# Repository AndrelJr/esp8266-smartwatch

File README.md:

# ESP8266 Smartwatch
## Pictures / Videos

#### YouTube Videos
* [Building the watch](https://www.youtube.com/watch?v=ve8lzYSVnGo)
* [Minetest controller](https://www.youtube.com/watch?v=W3ALEUs_7kA)
* [Compass test](https://www.youtube.com/watch?v=Mj3a6peVI30)

# Hardware
## Specifications
* ESP8266 with 32Mbit of flash memory
* MPU-9250 gyroscope, accelerometer with integrated AK8963 magnetometer
* RV-3029-C2 Real Time Clock
* FT232RQ for USB communication
* SSD1306 OLED Display, 128x64
* 3 Hardware Buttons
* MCP73831 LiPo charger
* 250mAh LiPo battery
* Dimensions: 35 * 39 * 11mm
* WiFi with chip antenna
* Vibration Motor

See `board/v1/README.md` for a detailed parts list.

# Software
The firmwares in `firmwares` use the [esp-open-sdk](https://github.com/pfalcon/esp-open-sdk). You may need to customize the `main.c` files to reflect your WiFi configuration. This is mainly a hardware project and not a software project, so the firmwares are primarily meant to be demos for the hardware features of the watch. Firmwares can be uploaded using [esptool](https://github.com/themadinventor/esptool) and debugging is possible with a serial port terminal like [espterm](https://github.com/Jeija/espterm).

# Attribution
* `libesphttpd` (used in the minetest firmware) was [written by Spritetm](https://github.com/Spritetm/libesphttpd) and contributors and is licensed under "THE BEER-WARE LICENSE".
* `httpclient.c` / `httpclient.h` (included in all firmwares) was [written by Caerbannog](https://github.com/Caerbannog/esphttpclient) and contributors and is licensed under "THE BEER-WARE LICENSE".
* `i2c_master.h` / `i2c_master.c` was written by Espressif Systems

# License
The hardware design (schematic, PCB design, footprints, ...) is licensed under a [Creative Commons Attribution-NonCommercial-ShareAlike 4.0 International License](http://creativecommons.org/licenses/by-nc-sa/4.0/) (CC-BY-NC-SA).

The firmware source code is licensed under the [MIT License](https://opensource.org/licenses/MIT).

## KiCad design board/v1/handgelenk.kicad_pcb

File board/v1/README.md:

# ESP8266 Smartwatch Hardware V1
## Parts list
* 1x PCB
* 1x ESP8266EX WiFi SoC
* 1x FT232RQ USB to UART
* 1x MCP73831 LiPo charger
* 1x TLV70233 SOT-23 LDO (or compatible)
* 1x W25Q32BV 32Mbit flash
* 1x InvenSense MPU-9250 9-axis sensor
* 1x RV-3029-C2 RTC
* 1x 26MHz crystal 2.5x2mm
* 1x Rainsun AN9520 Chip Antenna
* 3x TS-015A / WS-TUS 434331045822 Buttons
* 1x muRata BLM21PG 600 EMI Suppression Filter
* 1x USB Micro B connector, SMD
* 1x EastRising SSD1306 OLED
* 1x 250mAh LiPo
* 1x Low power vibration motor
* 1x BC849 SOT-23 NPN transistor
* 6x 100nF 0603 Capacitor
* 3x 10nF 0603 Capacitor
* 2x 4.7µF 0603 Capacitor
* 1x 100µF 1206 Capacitor
* 1x 10µF 1206 Capacitor
* 1x 5.6pF 0402 Capacitor
* 2x 10pF 0402 Capacitor
* 5x 1µF 0603 Capacitor
* 1x 2.2µF 0603 Capacitor
* 3x 1N4148 SOD-323 Diode
* 2x 1K 0603 Resistor
* 1x 12K 0603 Resistor
* 1x 3.3K 0603 Resistor
* 1x 300 0603 Resistor
* 1x 200 0603 Resistor
* 1x 330K 0603 Resistor
* 1x 100K 0603 Resistor
* 4x 10K 0603 Resistor
* 1x 50 0603 Resistor
* 1x 390K 0603 Resistor

## Production files
See the `gerber` directory for original PCB production files. My PCBs were manufactured by Seeedstudio's PCB service.

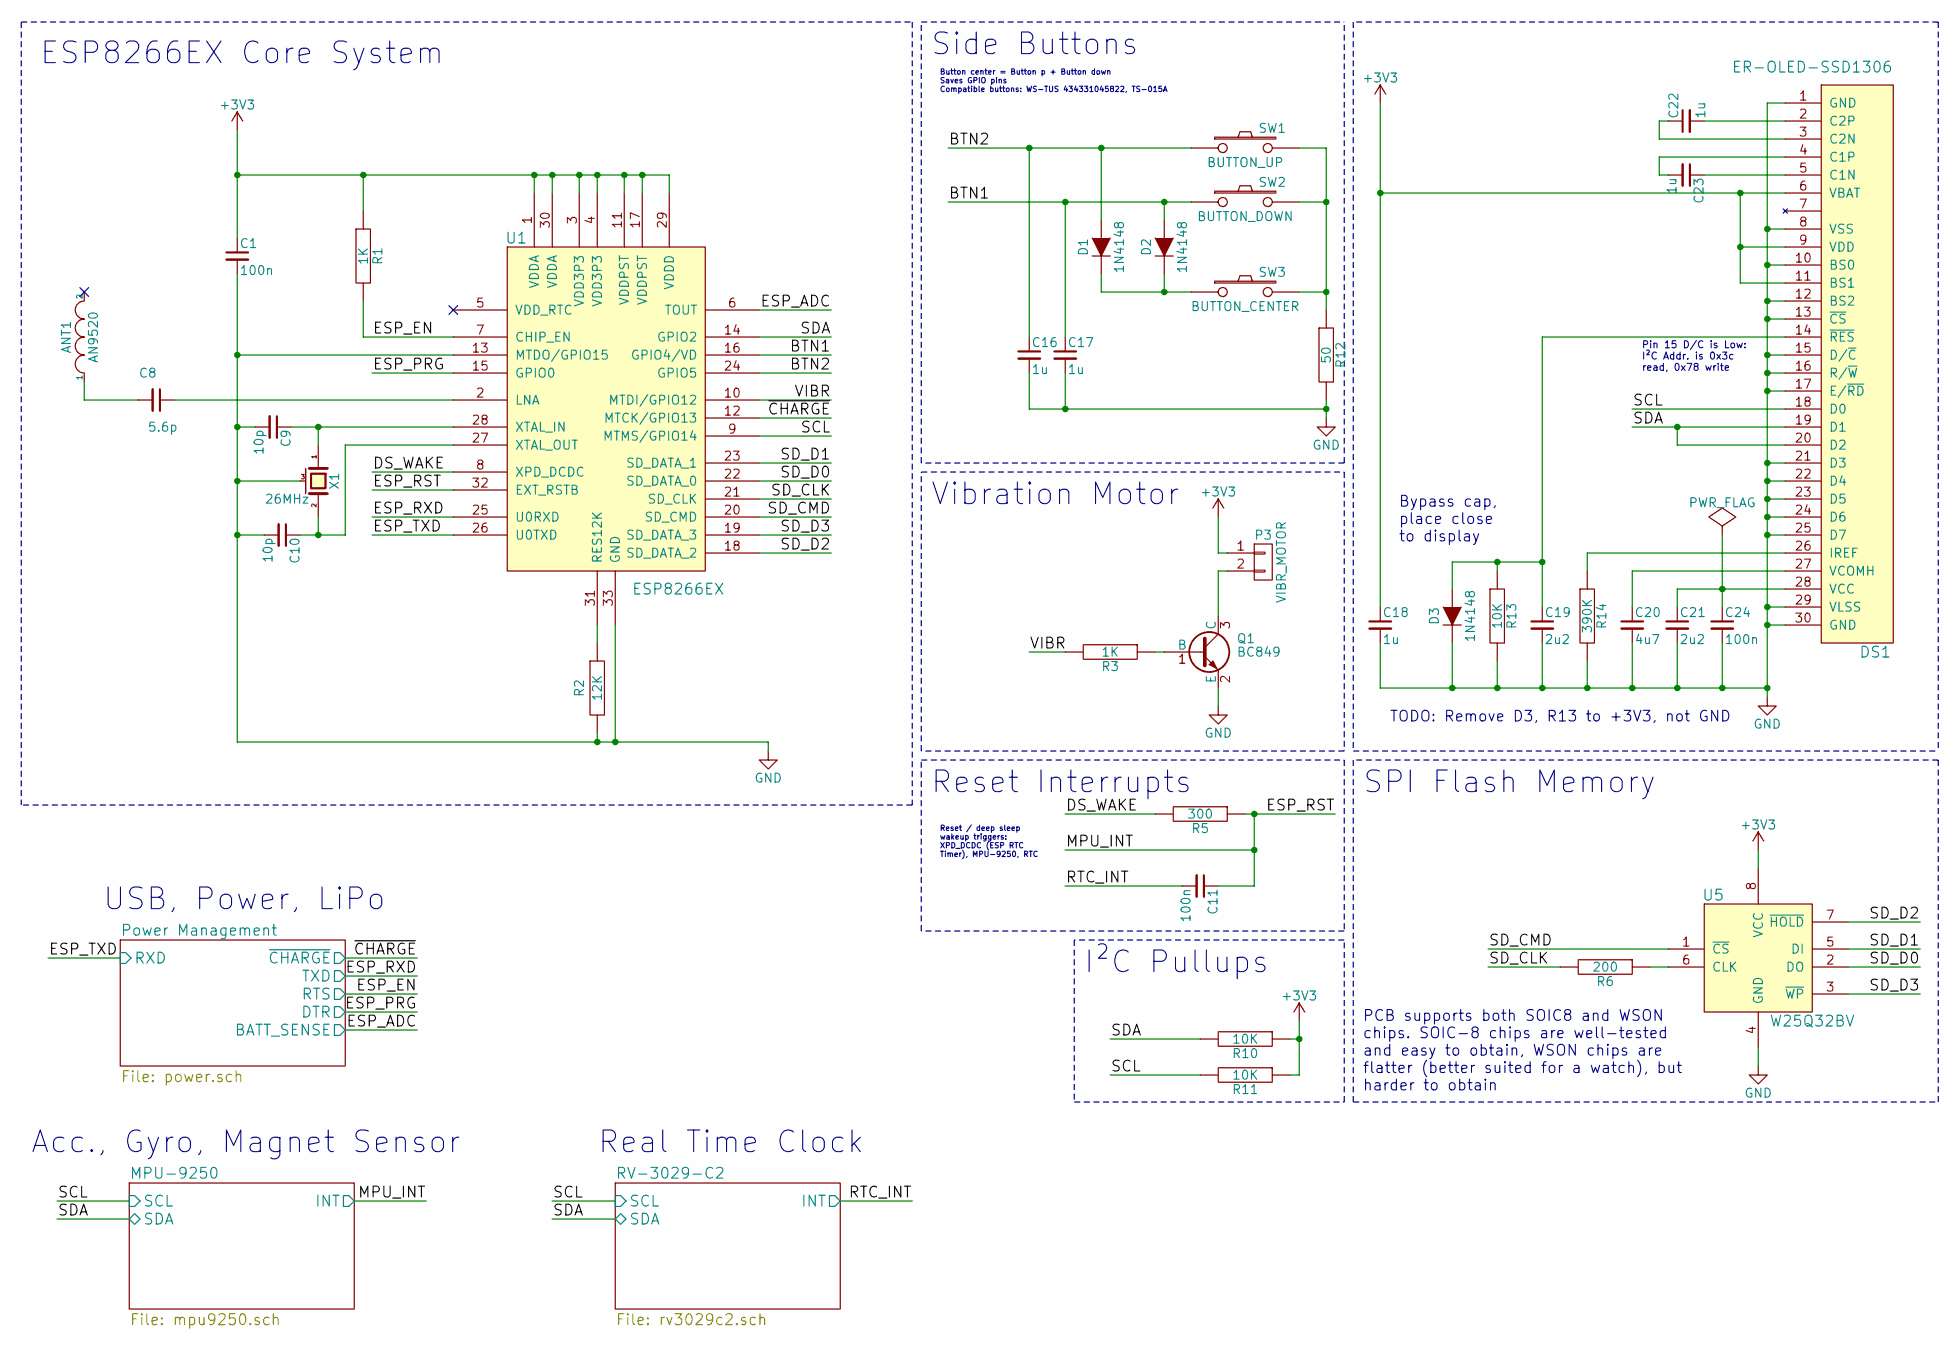
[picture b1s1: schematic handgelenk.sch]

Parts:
ANT1: AN9520; an9520
C1, C11, C24: 100n; C_0603
C8: 5.6p; C_0402
C9, C10: 10p; C_0402
C16, C17, C18, C22, C23: 1u; C_0603
C19, C21: 2u2; C_0603
C20: 4u7; C_0603
D1, D2, D3: 1N4148; SOD-323
DS1: ER-OLED-SSD1306; er-oled-ssd1306
P3: VIBR_MOTOR; Pin_Header_Straight_1x02
Q1: BC849; SOT-23
R1, R3: 1K; R_0603
R2: 12K; R_0603
R5: 300; R_0603
R6: 200; R_0603
R10, R11, R13: 10K; R_0603
R12: 50; R_0603
R14: 390K; R_0603
SW1: BUTTON_UP; ts015a
SW2: BUTTON_DOWN; ts015a
SW3: BUTTON_CENTER; ts015a
U1: ESP8266EX; QFN-32-1EP_5x5mm_Pitch0.5mm
U5: W25Q32BV; wson8_5x6
X1: 26MHz; crystal_2.5x2

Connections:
+3V3: C1.1, C18.1, DS1.6 (VBAT), DS1.9 (VDD), DS1.11 (BS1), P3.1, R1.1, R10.1, R11.1, U1.1 (VDDA), U1.3 (VDD3P3), U1.4 (VDD3P3), U1.11 (VDDPST), U1.17 (VDDPST), U1.29 (VDDD), U1.30 (VDDA), U5.8 (VCC); also elsewhere on the board
/BTN1: C17.1, D2.2 (A), SW2.1, U1.16 (GPIO4/VD)
/BTN2: C16.1, D1.2 (A), SW1.1, U1.24 (GPIO5)
/DS_WAKE: R5.2, U1.8 (XPD_DCDC)
/MPU-9250/INT: C11.1, R5.1, U1.32 (EXT_RSTB); also elsewhere on the board
/MPU-9250/SCL: DS1.18 (D0), R11.2, U1.9 (MTMS/GPIO14); also elsewhere on the board
/MPU-9250/SDA: DS1.19 (D1), DS1.20 (D2), R10.2, U1.14 (GPIO2); also elsewhere on the board
/Power Management/BATT_SENSE: U1.6 (TOUT); also elsewhere on the board
/Power Management/DTR: U1.15 (GPIO0); also elsewhere on the board
/Power Management/RTS: R1.2, U1.7 (CHIP_EN); also elsewhere on the board
/Power Management/RXD: U1.26 (U0TXD); also elsewhere on the board
/Power Management/TXD: U1.25 (U0RXD); also elsewhere on the board
/Power Management/~CHARGE: U1.12 (MTCK/GPIO13); also elsewhere on the board
/RV-3029-C2/INT: C11.2; also elsewhere on the board
/SD_CLK: R6.2, U1.21 (SD_CLK)
/SD_CMD: U1.20 (SD_CMD), U5.1 (~CS)
/SD_D0: U1.22 (SD_DATA_0), U5.2 (DO)
/SD_D1: U1.23 (SD_DATA_1), U5.5 (DI)
/SD_D2: U1.18 (SD_DATA_2), U5.7 (~HOLD)
/SD_D3: U1.19 (SD_DATA_3), U5.3 (~WP)
/VIBR: R3.2, U1.10 (MTDI/GPIO12)
GND: C1.2, C9.2, C10.2, C16.2, C17.2, C18.2, C19.2, C20.2, C21.2, C24.2, D3.1 (K), DS1.1 (GND), DS1.8 (VSS), DS1.10 (BS0), DS1.12 (BS2), DS1.13 (~CS), DS1.15 (D/~C), DS1.16 (R/~W), DS1.17 (E/~RD), DS1.21 (D3), DS1.22 (D4), DS1.23 (D5), DS1.24 (D6), DS1.25 (D7), DS1.29 (VLSS), DS1.30 (GND), Q1.2 (E), R2.2, R12.2, R13.2, R14.2, U1.13 (MTDO/GPIO15), U1.33 (GND), U5.4 (GND), X1.3 (case); also elsewhere on the board
unnamed: ANT1.1, C8.2
unnamed: C8.1, U1.2 (LNA)
unnamed: C9.1, U1.28 (XTAL_IN), X1.1
unnamed: C10.1, U1.27 (XTAL_OUT), X1.2
unnamed: C19.1, D3.2 (A), DS1.14 (~RES), R13.1
unnamed: C20.1, DS1.27 (VCOMH)
unnamed: C21.1, C24.1, DS1.28 (VCC)
unnamed: C22.1, DS1.3 (C2N)
unnamed: C22.2, DS1.2 (C2P)
unnamed: C23.1, DS1.5 (C1N)
unnamed: C23.2, DS1.4 (C1P)
unnamed: D1.1 (K), D2.1 (K), SW3.1
unnamed: DS1.26 (IREF), R14.1
unnamed: P3.2, Q1.3 (C)
unnamed: Q1.1 (B), R3.1
unnamed: R2.1, U1.31 (RES12K)
unnamed: R6.1, U5.6 (CLK)
unnamed: R12.1, SW1.2, SW2.2, SW3.2

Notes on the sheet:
Reset / deep sleep wakeup triggers: XPD_DCDC (ESP RTC Timer), MPU-9250, RTC
PCB supports both SOIC8 and WSON chips. SOIC-8 chips are well-tested and easy to obtain, WSON chips are flatter (better suited for a watch), but harder to obtain
SPI Flash Memory
Pin 15 D/C is Low: I²C Addr. is 0x3c read, 0x78 write
Bypass cap, place close to display
Button center = Button p + Button down Saves GPIO pins Compatible buttons: WS-TUS 434331045822, TS-015A
Side Buttons
Vibration Motor
ESP8266EX Core System
I²C Pullups
Reset Interrupts
Acc., Gyro, Magnet Sensor
Real Time Clock
USB, Power, LiPo
TODO: Remove D3, R13 to +3V3, not GND

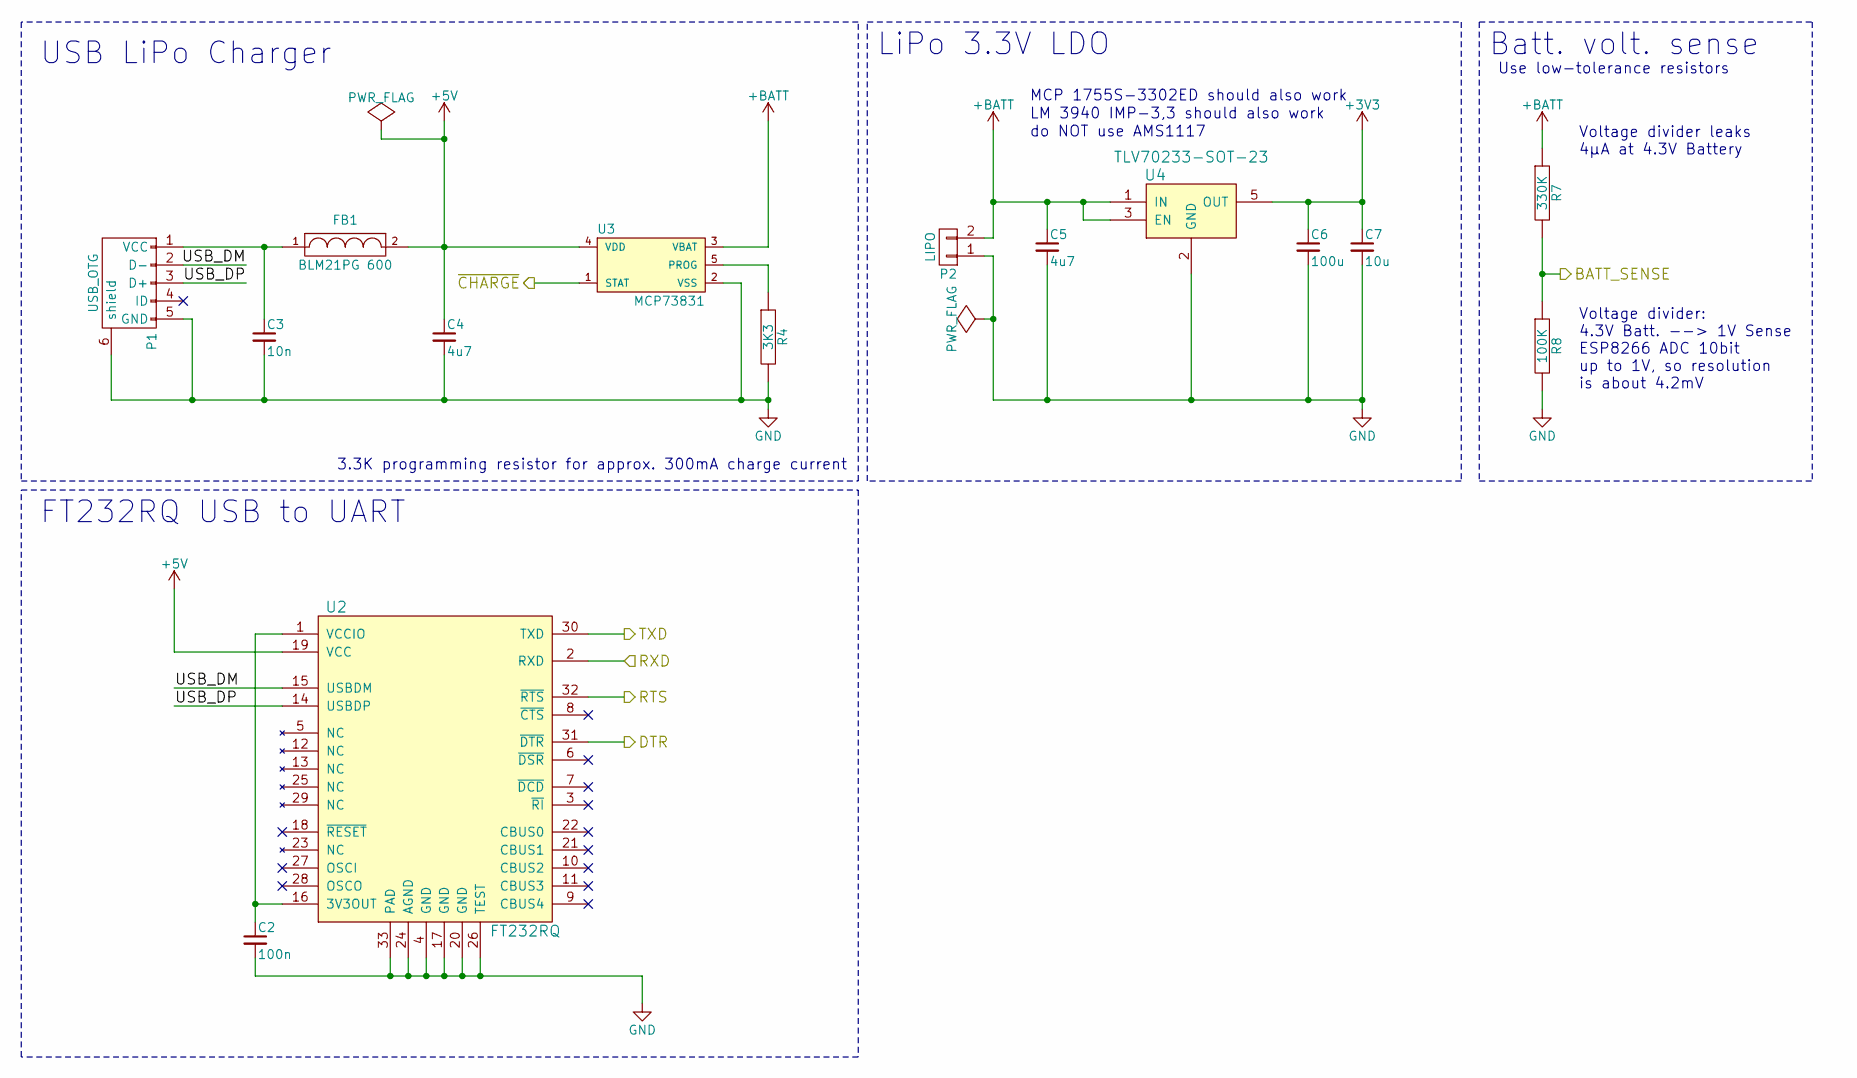
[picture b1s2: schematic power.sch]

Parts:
C2: 100n; C_0603
C3: 10n; C_0603
C4, C5: 4u7; C_0603
C6: 100u; C_1206
C7: 10u; C_0603
FB1: BLM21PG 600; C_0805
P1: USB_OTG; USB_Micro-B
P2: LIPO; Pin_Header_Straight_1x02
R4: 3K3; R_0603
R7: 330K; R_0603
R8: 100K; R_0603
U2: FT232RQ; QFN-32-1EP_5x5mm_Pitch0.5mm
U3: MCP73831; SOT-23-5
U4: TLV70233-SOT-23; SOT-23-5

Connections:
+3V3: C6.1, C7.1, U4.5 (OUT); also elsewhere on the board
+5V: C4.1, FB1.2, U2.19 (VCC), U3.4 (VDD)
+BATT: C5.1, P2.2, R7.1, U3.3 (VBAT), U4.1 (IN), U4.3 (EN)
/Power Management/BATT_SENSE: R7.2, R8.1; also elsewhere on the board
/Power Management/DTR: U2.31 (~DTR); also elsewhere on the board
/Power Management/RTS: U2.32 (~RTS); also elsewhere on the board
/Power Management/RXD: U2.2 (RXD); also elsewhere on the board
/Power Management/TXD: U2.30 (TXD); also elsewhere on the board
/Power Management/USB_DM: P1.2 (D-), U2.15 (USBDM)
/Power Management/USB_DP: P1.3 (D+), U2.14 (USBDP)
/Power Management/~CHARGE: U3.1 (STAT); also elsewhere on the board
GND: C2.2, C3.2, C4.2, C5.2, C6.2, C7.2, P1.5 (GND), P1.6 (shield), P2.1, R4.2, R8.2, U2.4 (GND), U2.17 (GND), U2.20 (GND), U2.24 (AGND), U2.26 (TEST), U2.33 (PAD), U3.2 (VSS), U4.2 (GND); also elsewhere on the board
unnamed: C2.1, U2.1 (VCCIO), U2.16 (3V3OUT)
unnamed: C3.1, FB1.1, P1.1 (VCC)
unnamed: R4.1, U3.5 (PROG)

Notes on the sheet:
do NOT use AMS1117
LM 3940 IMP-3,3 should also work
MCP 1755S-3302ED should also work
3.3K programming resistor for approx. 300mA charge current
LiPo 3.3V LDO
USB LiPo Charger
FT232RQ USB to UART
Batt. volt. sense
Use low-tolerance resistors
Voltage divider: 4.3V Batt. --> 1V Sense ESP8266 ADC 10bit up to 1V, so resolution is about 4.2mV
Voltage divider leaks 4µA at 4.3V Battery

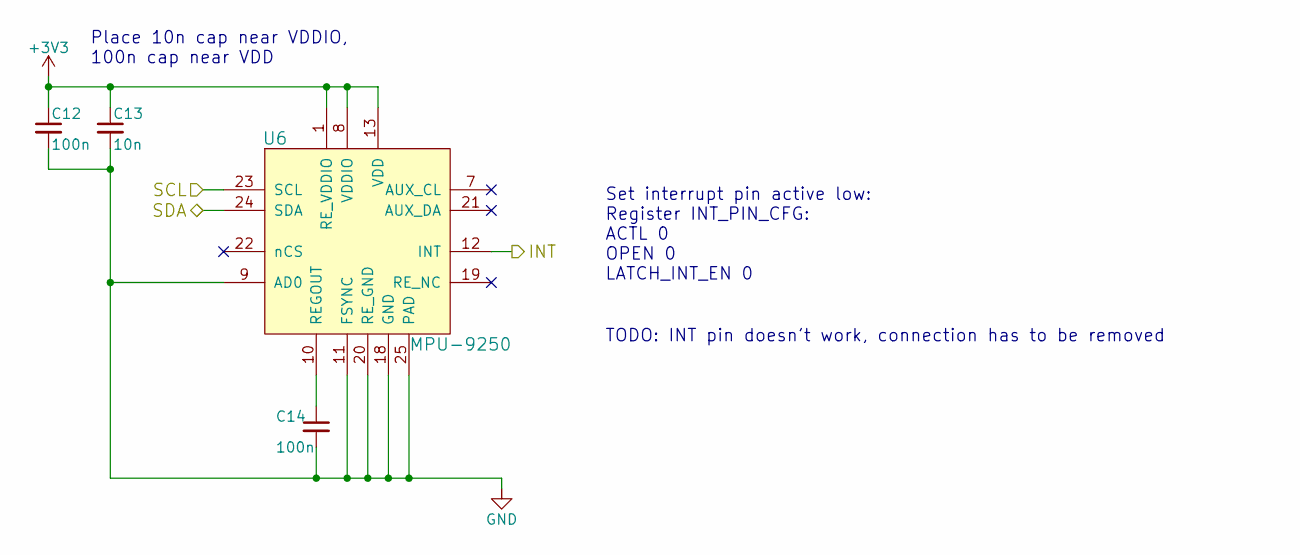
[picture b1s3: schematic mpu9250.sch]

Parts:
C12, C14: 100n; C_0603
C13: 10n; C_0603
U6: MPU-9250; QFN-24-1EP_3x3mm_Pitch0.4mm

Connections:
+3V3: C12.1, C13.1, U6.1 (RE_VDDIO), U6.8 (VDDIO), U6.13 (VDD); also elsewhere on the board
/MPU-9250/INT: U6.12 (INT); also elsewhere on the board
/MPU-9250/SCL: U6.23 (SCL); also elsewhere on the board
/MPU-9250/SDA: U6.24 (SDA); also elsewhere on the board
GND: C12.2, C13.2, C14.2, U6.9 (AD0), U6.11 (FSYNC), U6.18 (GND), U6.20 (RE_GND), U6.25 (PAD); also elsewhere on the board
unnamed: C14.1, U6.10 (REGOUT)

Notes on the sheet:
Place 10n cap near VDDIO, 100n cap near VDD
Set interrupt pin active low: Register INT_PIN_CFG: ACTL 0 OPEN 0 LATCH_INT_EN 0
TODO: INT pin doesn't work, connection has to be removed

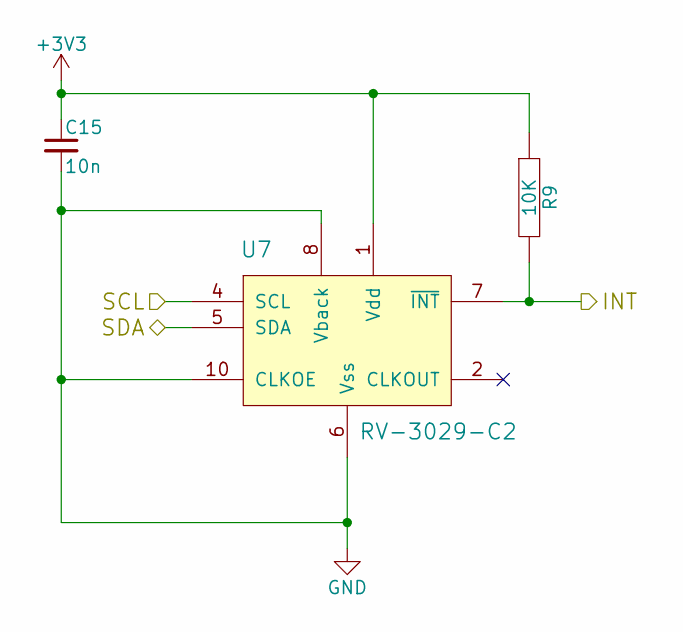
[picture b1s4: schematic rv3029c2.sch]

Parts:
C15: 10n; C_0603
R9: 10K; R_0603
U7: RV-3029-C2; rv3029

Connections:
+3V3: C15.1, R9.1, U7.1 (Vdd); also elsewhere on the board
/MPU-9250/SCL: U7.4 (SCL); also elsewhere on the board
/MPU-9250/SDA: U7.5 (SDA); also elsewhere on the board
/RV-3029-C2/INT: R9.2, U7.7 (~INT); also elsewhere on the board
GND: C15.2, U7.6 (Vss), U7.8 (Vback), U7.10 (CLKOE); also elsewhere on the board

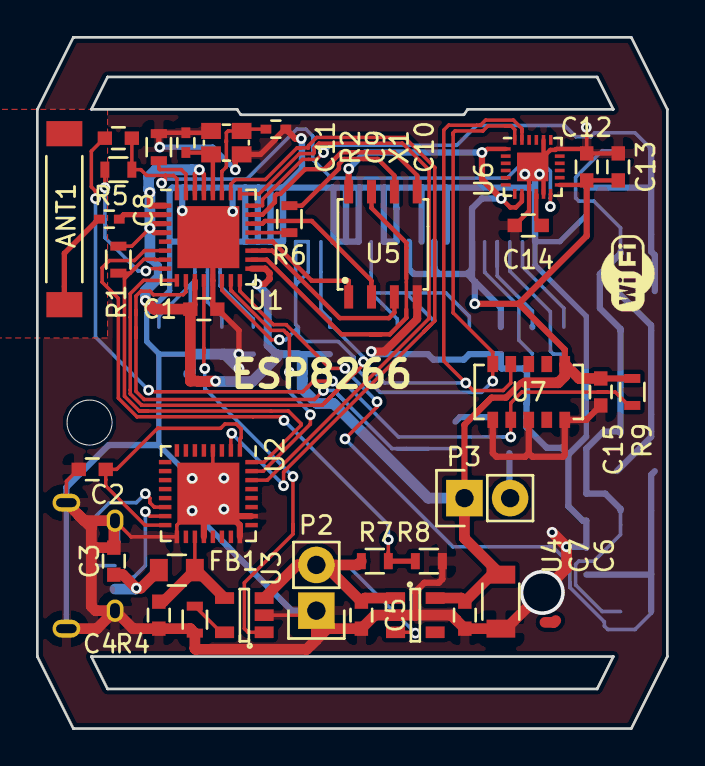
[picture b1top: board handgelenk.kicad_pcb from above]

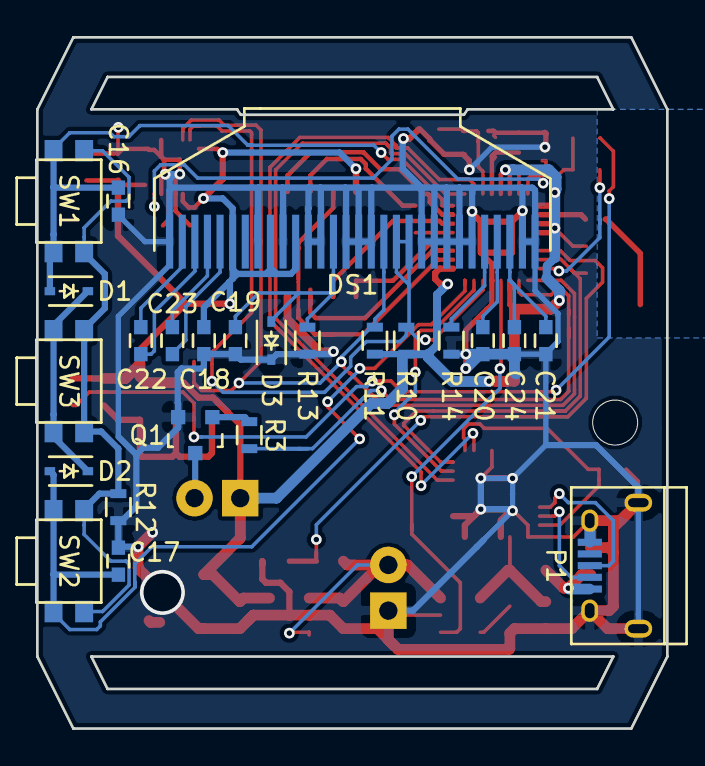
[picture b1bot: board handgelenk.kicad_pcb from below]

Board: 2 copper layers, 35.0 x 38.4 mm, 59 parts (24 on the bottom side), 48 nets.

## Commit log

2016-03-11 Initial Upload - Hardware, software, production files, BOM, ...
